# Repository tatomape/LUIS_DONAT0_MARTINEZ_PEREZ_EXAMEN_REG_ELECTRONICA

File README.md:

# LUIS_DONAT0_MARTINEZ_PEREZ_EXAMEN_REG_ELECTRONICA

Profesor:Erick Moreno Negrete
Institución: Tecnológico Salesiano Carlos Gómez
Asignatura: Simulación Electrónica y Tecnología y Taller de Electronica
Fecha: 26 de Junio de 2026
Objetivo del Proyecto
Diseñar, analizar analíticamente, simular y desarrollar el diseño de circuito impreso (PCB) de un convertidor reductor (Buck Converter) síncrono de una fase, empleando herramientas de software profesional (Multisim y KiCad) y justificando técnicamente la selección de componentes mediante hojas de datos.
Problema Asignado:
Se analiza un convertidor reductor de una fase operando bajo los siguientes parámetros nominales:
Voltaje de entrada (VG): 48 V
Voltaje de salida (Vo): 12 V
Inductancia : 220 uH
Capacitancia : 470 uF
Resistencia de carga : 12 Ohms
Frecuencia de conmutación : 50 kHz
Metodología Utilizada
1. Cálculo Teórico: Deducción de ecuaciones fundamentales del convertidor Buck en Modo de Conducción Continua (MCC).
2. Simulación en Multisim: Implementación del circuito esquemático con parámetros reales para evaluar transitorios de arranque y estado estable.
3. Análisis Comparativo: Evaluación del error porcentual entre la teoría matemática y las mediciones simuladas.
4. Diseño en KiCad: Creación de esquemático y ruteo de la PCB considerando planos de tierra y anchos de pista óptimos para potencia.
Resultados Obtenidos (Resumen)
Variable | Valor Teórico | Valor Simulado | Error (%)
Ciclo de trabajo (D): 0.25 (25%)
Voltaje de Salida (Vo): 12.0 V
Corriente de Salida (Io): 1.0 A
Rizado de Corriente (Delta iL): 0.8182 A
Corriente Máxima (iL,max): 1.4091 A
Corriente Mínima (iL,min): 0.5909 A
Rizado de Voltaje (Delta Vo): 4.352 mV
Rizado (%): 0.0363 %
Conclusiones
El convertidor opera exitosamente en Modo de Conducción Continua (MCC) debido a que la corriente mínima en el inductor (0.5909 A) es estrictamente mayor que cero. El rizado de tensión teórico obtenido (4.352 mV) demuestra un excelente filtrado por parte del capacitor de 470 uF. La implementación del driver NCP81253 asegura que la señal PWM de 5V sea capaz de conmutar adecuadamente al MOSFET de potencia RFD3055LE superando las capacidades parásitas de compuerta.

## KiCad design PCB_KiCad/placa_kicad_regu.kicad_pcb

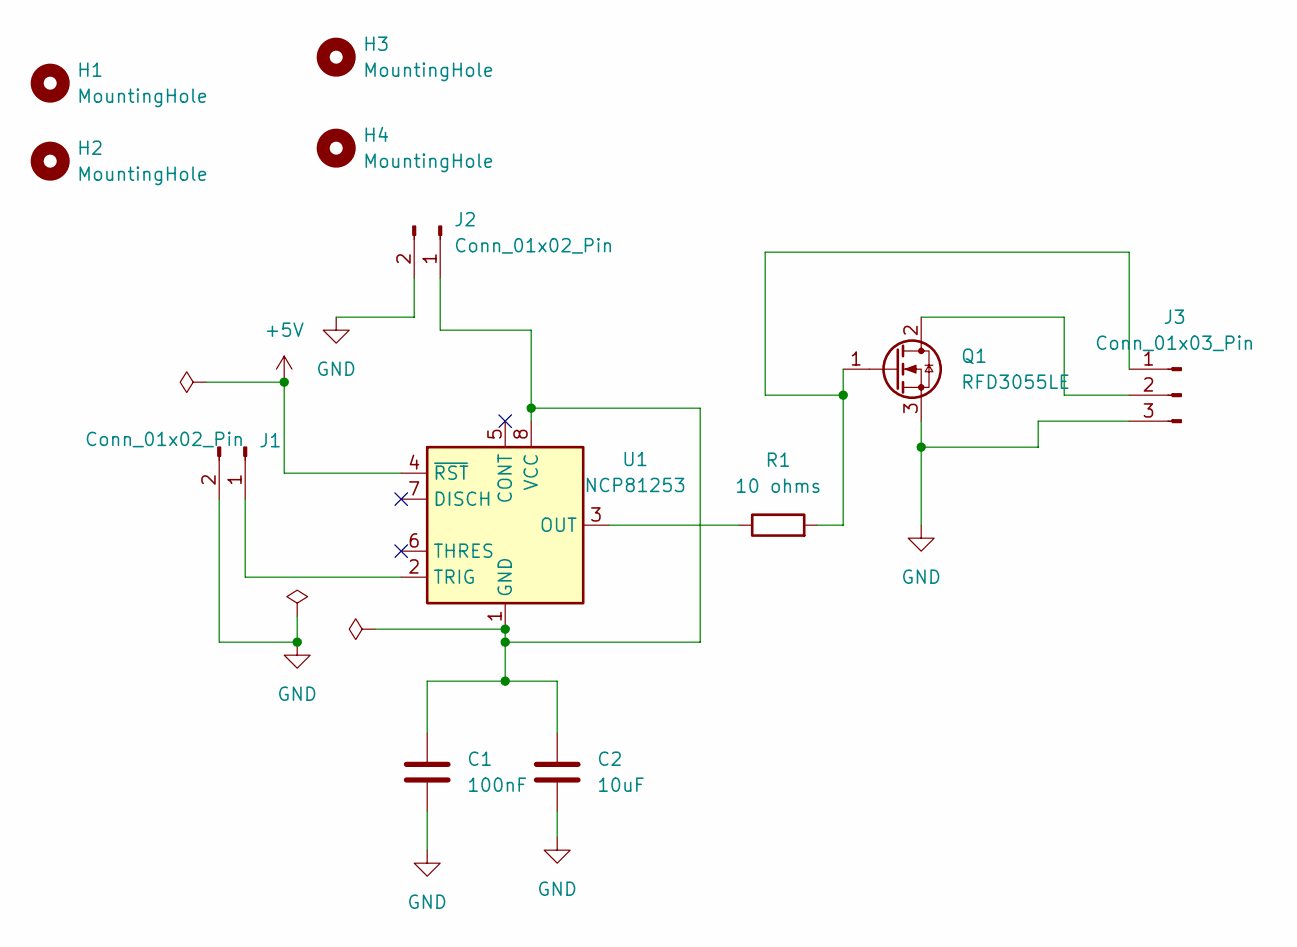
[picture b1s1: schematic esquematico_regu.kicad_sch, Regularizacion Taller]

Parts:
C1: 100nF; C_0805_2012Metric
C2: 10uF; C_0805_2012Metric
H1, H2, H3, H4: MountingHole; MountingHole_2.2mm_M2
J1, J2: Conn_01x02_Pin; PinHeader_1x02_P1.00mm_Vertical
J3: Conn_01x03_Pin; PinHeader_1x03_P1.00mm_Vertical
Q1: RFD3055LE; TO-220-3_Vertical
R1: 10 ohms; R_0805_2012Metric
U1: NCP81253; SOIC-8_3.9x4.9mm_P1.27mm

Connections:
+5V: U1.4 (~RST)
GND: C1.2, C2.2, J1.2, J2.2, J3.3, Q1.3 (S)
unnamed: J1.1, U1.2 (TRIG)
unnamed: C1.1, C2.1, J2.1, U1.1 (GND), U1.8 (VCC)
unnamed: J3.1, Q1.1 (G), R1.2
unnamed: J3.2, Q1.2 (D)
unnamed: R1.1, U1.3 (OUT)

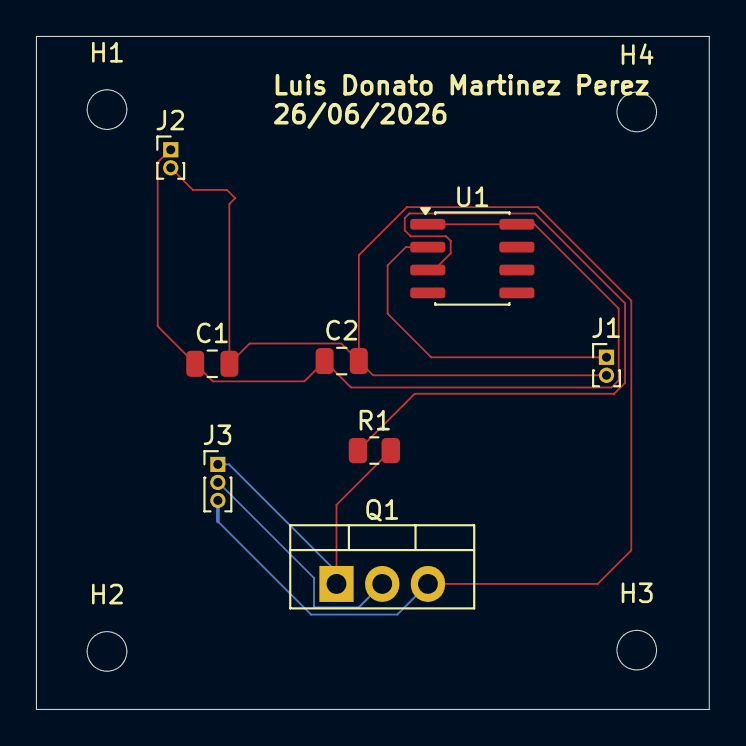
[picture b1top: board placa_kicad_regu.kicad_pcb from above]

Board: 2 copper layers, 37.4 x 37.4 mm, 12 parts (0 on the bottom side), 6 nets.

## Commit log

2026-06-25 Create Evidencias
2026-06-25 Update Evidencias
2026-06-26 Rename Calculos/Capture0.png to Calculo
